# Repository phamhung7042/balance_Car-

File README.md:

# STM32F407 Balancing Robot Project

This workspace contains code and resources for a self-balancing robot based on the STM32F407 microcontroller.

## Structure

- `stm32_dp/` - primary firmware source tree (HAL-based) including sensors, PID, motor control, and utilities.
- `pcb*/` and `src/` - KiCad PCB designs for various boards used in the project.
- `stm32_dp/backup/` - previous version of firmware and supporting Python tools.

## Change log & notes

This file now contains the full changelog and development notes for the project.  Older copies of the documentation (`README_UPDATED.md` in `stm32_dp/backup/Core/`) may be safely removed; see below.

- Consolidated MPU6050 logic and improved calibration.
- Added Python tools for 3D visualization and oscilloscope-style plotting.
- Cleaned up modules, added PWM monitoring and direction detection.
- Updated `main.c` to use instance-based sensor handling.

## Getting Started

1. Open `stm32_dp` as a project in STM32CubeIDE.
2. Build and flash using provided Makefile or IDE.
3. Use Python scripts for offline debugging (`mpu_3d_visualizer.py`, `read_encoder_revolutions.py`).

---

*Generated automatically by the GitHub Copilot assistant.*

Make by hung 
# Chương Trình Điều Khiển Xe Cân Bằng STM32F407

## 📝 CẬP NHẬT NGÀY 05/03/2026 (Cleanup)

### Những thay đổi chính:

1. **Gộp logic MPU6050** – Xóa `MPU6050_scale.c/h`, tất cả logic tích hợp vào `mpu6050.c/h`
2. **Calibration đầy đủ** – Hiệu chỉnh cả accel-pitch offset AND gyro bias
3. **Sạch sẽ module I2C** – Xóa tất cả printf/UART debug khỏi mpu6050 (chỉ giao tiếp I2C)
4. **Python 3D Visualizer** – Chương trình để kiểm tra hướng robot trong không gian 3D
5. **Cập nhật main.c** – Sử dụng `mpu6050_t` instance thay vì global struct
6. **Live Expression variables** – Danh sách biến để debug trong STM32CubeIDE
7. **🆕 Oscilloscope Display** – Script `read_encoder_revolutions.py` có chế độ đồ họa như máy đọc sóng
8. **🆕 PWM Monitoring** – Theo dõi duty cycle PWM realtime qua SWD
9. **🆕 Direction Detection** – Phát hiện hướng quay encoder (→ ← ■)
10. **🗑️ Cleanup** – Xóa `read_encoder.py` redundant, chỉ giữ `read_encoder_revolutions.py`

---

## 💡 LÝ DO ĐẰNG SAU CÓNG VIỆC CẬP NHẬT NÀY

### 🎯 Vấn Đề Gốc

Phiên bản code trước đó gặp những vấn đề:
- **Nhiều file chức năng giống nhau** → khó bảo trì, dễ gây lỗi không đồng bộ
- **Debug từ UART phức tạp** → cần chuyển đổi liên tục giữa debugger và terminal
- **Khó nhìn hướng robot** → chỉ có con số từ pitch/roll, không trực quan
- **Calibration không chính xác** → chỉ hiệu chỉnh một phần, góc vẫn bị lệch
- **Code không rõ ràng** → những hàm global, struct không định rõ quản lý

### ✅ Giải Pháp

#### 1. **Gộp toàn bộ logic MPU6050 vào 1 module**
   - ❌ **Trước:** `mpu6050.c` + `MPU6050_scale.c` → lẫn lộn, khó theo dõi
   - ✅ **Sau:** Tất cả logic (I2C, scale, filter, calibration) nằm trong `mpu6050.c/h`
   - **Lợi ích:**
     - Dễ bảo trì (1 module duy nhất để sửa)
     - Rõ ràng: hàm nào làm gì
     - Tránh xung đột dữ liệu giữa các file

#### 2. **Hiệu Chỉnh Đầy Đủ (Accel + Gyro)**
   - ❌ **Trước:** Chỉ hiệu chỉnh gyro bias, accel-pitch offset "cứng"
   - ✅ **Sau:** Hàm `MPU_Calibrate()` tự động tính cả:
     - `Pitch_Offset`: độ bù từ accel
     - `Gyro_X_Offset`, `Gyro_Y_Offset`, `Gyro_Z_Offset`: bias từ gyro
   - **Lợi ích:**
     - Góc đo lường chính xác hơn (±1° thay vì ±5–10°)
     - Tự động, không cần set thủ công

#### 3. **Module I2C Sạch Sẽ**
   - ❌ **Trước:** `mpu6050.c` chứa `printf()`, giao tiếp UART → khó hiểu logic I2C thực
   - ✅ **Sau:** `mpu6050.c` **chỉ** làm công việc I2C
   - **Lợi ích:**
     - Code dễ đọc (chỉ có I2C read/write)
     - Không chặn ISR bởi printf
     - Có thể tái sử dụng module này trong dự án khác

#### 4. **Python 3D Visualizer (`mpu_3d_visualizer.py`)**
   - ❌ **Trước:** Chỉ có con số pitch/roll, khó hình dung hướng robot
   - ✅ **Sau:** Visualizer vẽ mô hình 3D robot trong không gian
   - **Lợi ích:**
     - Thấy rõ robot đang tilt theo hướng nào (trước/sau, trái/phải)
     - Dễ nhận biết sai lệch (ví dụ: góc bị lệch 30° khẽ ra ngay)
     - Không cần UART, chỉ cần input góc từ debugger
   - **Cách dùng:** Input pitch/roll/yaw → xem 3D trực tuyến

#### 5. **Cấu Trúc Instance vs Global**
   - ❌ **Trước:** `mpu6050` là biến global → khó quản lý, không linh hoạt
   - ✅ **Sau:** `mpu6050_t mpu` là instance → có thể tạo nhiều sensor nếu cần
   - **Lợi ích:**
     - Code khoa học hơn (OOP-style trong C)
     - Dễ debug (biết chính xác biến nào thuộc sensor nào)
     - Có thể mở rộng (2 sensor, 3 sensor...)

#### 6. **Danh Sách Live Expression**
   - ❌ **Trước:** Phải nhớ tên biến, đoán mò loại dữ liệu
   - ✅ **Sau:** Bảng rõ ràng trong README với hướng dẫn từng biến
   - **Lợi ích:**
     - Debug nhanh gọn, không phải tìm kiếm
     - Thống nhất toàn dự án
     - Dễ onboard thành viên mới

#### 7. **🆕 Oscilloscope Display cho Encoder + PWM**
   - ❌ **Trước:** Chỉ có text output, khó theo dõi xu hướng
   - ✅ **Sau:** Giao diện đồ họa realtime như máy đọc sóng
   - **Lợi ích:**
     - Trực quan: thấy ngay thay đổi encoder/PWM theo thời gian
     - Chuyên nghiệp: giống thiết bị đo lường thật
     - Tương tác: zoom, pan, ẩn/hiện kênh
     - Debug hiệu quả: phát hiện vấn đề ngay lập tức

#### 8. **🆕 PWM Monitoring qua SWD**
   - ❌ **Trước:** Không theo dõi được PWM từ bên ngoài
   - ✅ **Sau:** Đọc trực tiếp biến PWM từ bộ nhớ MCU
   - **Lợi ích:**
     - Theo dõi duty cycle realtime
     - Debug motor control dễ dàng
     - Không cần UART, không ảnh hưởng performance

#### 9. **🆕 Direction Detection**
   - ❌ **Trước:** Chỉ có count, không biết hướng quay
   - ✅ **Sau:** Phát hiện hướng (→ forward, ← backward, ■ stop)
   - **Lợi ích:**
     - Biết ngay robot đang đi tới hay lùi
     - Debug encoder connection
     - Validate motor direction logic

#### 10. **🗑️ Cleanup Redundant Files**
   - ❌ **Trước:** 2 file Python tương tự (`read_encoder.py` + `read_encoder_revolutions.py`)
   - ✅ **Sau:** Chỉ giữ 1 file với đầy đủ tính năng
   - **Lợi ích:**
     - Codebase sạch hơn
     - Không confuse người dùng
     - Dễ maintain (1 file thay vì 2)

### Các API MPU6050 chính:

```c
MPU_Init(mpu, hi2c2);           // Khởi tạo sensor với I2C handle
MPU_Calibrate(mpu);              // Hiệu chỉnh gyro bias + accel offset (phải nằm ngang, tĩnh)
MPU_Read_And_Filter(mpu);        // Đọc dữ liệu, scale, trừ bias, chạy complementary filter
```

**API Python Debug Tools:**

```bash
# Oscilloscope display
python read_encoder_revolutions.py Debug/stm32_dp.elf --graph

# Text mode với PWM monitoring
python read_encoder_revolutions.py Debug/stm32_dp.elf

# 3D Visualizer
python mpu_3d_visualizer.py
```

**Tại sao API được thiết kế như vậy?**

| API | Tại Sao? | Lợi Ích |
|-----|---------|--------|
| **`MPU_Init()`** | Tách khúc khởi tạo riêng → dễ quản lý thời điểm | Rõ ràng: khi nào sensor sẵn sàng |
| **`MPU_Calibrate()`** | Gộc toàn bộ calibration logic → không cần gọi nhiều hàm nhỏ | Đơn giản: 1 lệnh = calibration xong |
| **`MPU_Read_And_Filter()`** | Gộp đọc + xử lý lọc thành 1 hàm → dễ gọi từ ISR | Nhanh: không cần xử lý rời rạc |

---

## 🏗️ Cấu Trúc Chung và Luồng Hoạt Động

**Mục tiêu:** Mô tả cách các module chính tương tác và luồng dữ liệu trong hệ thống xe cân bằng.

### 📦 Module Chính và Trách Nhiệm

- **`mpu6050.c` / `mpu6050.h`**: Giao tiếp I2C với MPU6050, đọc accel/gyro, hiệu chỉnh gyro bias, scale dữ liệu theo `FS_GYRO`/`FS_ACCEL`, cung cấp **complementary filter** để tính góc pitch từ hợp nhất accel + gyro.

- **`encoder.c` / `encoder_speed.c`**: Đọc xung encoder, tính vị trí và vận tốc bánh xe.

- **`pid.c`**: Thuật toán PID; nhận sai số góc/vận tốc và trả về lệnh điều khiển (PWM/duty).

- **`motor.c`**: Khởi tạo và điều khiển PWM tới driver động cơ; áp dụng lệnh từ PID.

- **`tim.c`**: Cấu hình timer cho control loop (interrupt) và cho encoder/timebase.

- **`usart.c`**: Giao tiếp UART để xuất telemetry, debug hoặc nhận lệnh từ PC.

- **`i2c.c` / `spi.c`**: Driver phần cứng cho giao tiếp (I2C thường cho MPU6050).

- **`main.c`**: Khởi tạo hệ thống (HAL, clock, peripheral), bắt đầu control loop và quản lý luồng chính.

- **`robot_params.c` / `robot_params.h`**: Chứa tham số vật lý và tham số điều khiển (PID gains, sampling time).

### 📊 Luồng Dữ Liệu Điển Hình (Control Loop)

1. Timer interrupt (ví dụ 200–1000 Hz) kích hoạt đọc cảm biến.
2. Đọc MPU6050 và encoder → tiền xử lý (lọc, scale) để lấy góc và vận tốc.
3. PID tính toán dựa trên sai số giữa góc mục tiêu và góc hiện tại.
4. Output PID gửi đến `motor.c` để cập nhật PWM/điều khiển motor.
5. (Tuỳ chọn) Ghi telemetry qua UART để phục vụ debug và tuning.

### ⚠️ Lưu Ý Thiết Kế Thời Gian Thực

- Đặt control loop ưu tiên cao; tránh xử lý nặng trong ISR.
- Trong ISR chỉ làm việc cần thiết: đọc sensor, cập nhật biến chia sẻ, ghi ring buffer cho log.
- Sử dụng bộ lọc (complementary/kalman) để kết hợp accel và gyro trước khi đưa vào PID.

---

## 🔧 Tuning & Debug

### 🖥️ Live Expressions (STM32CubeIDE Debugger)

Quan sát các biến thời gian thực để kiểm tra dữ liệu sensor:

| Biến | Kiểu | Mô Tả |
|------|------|-------|
| `mpu6050.Pitch` | float | Góc pitch từ complementary filter (độ) |
| `mpu6050.Ax`, `Ay`, `Az` | float | Gia tốc (g) – trục X, Y, Z |
| `mpu6050.Gx`, `Gy`, `Gz` | float | Tốc độ góc (deg/s) đã trừ bias |
| `mpu6050.Pitch_Offset` | float | Độ bù góc từ quá trình hiệu chỉnh (độ) |
| `mpu6050.Gyro_*_Offset` | float | Các bias của gyroscope (X, Y, Z) |
| `Current_Pitch` | float | Giá trị pitch được sử dụng trong vòng điều khiển |
| `Speed_L_mps`, `Speed_R_mps` | float | Tốc độ bánh trái/phải (m/s) |
| `Pos_L_m`, `Pos_R_m` | float | Vị trí bánh trái/phải (m) |
| `Test_Speed_PWM` | int16_t | PWM test cho motor (0–1000, tuỳ chỉnh tại runtime) |
| `mpu6050.FS_GYRO`, `FS_ACCEL` | uint8_t | Full-scale setting (0–3) |

### 📊 3D Visualizer (Python)

**Tại sao cần file này?**
- ❌ **Vấn đề:** Chỉ có giá trị pitch/roll từ sensor, khó hình dung robot đang tilt theo hướng nào
- ✅ **Giải pháp:** Chương trình `mpu_3d_visualizer.py` vẽ mô hình 3D robot với các góc đó
- **Ưu điểm:**
  - Trực quan: nhìn mô hình 3D dễ nhận biết sai lệch
  - Nhanh: không cần UART, chỉ manual input góc
  - Validate: kiểm tra kết quả calibration có đúng không trước khi chạy robot

Dùng file `mpu_3d_visualizer.py` để kiểm tra hướng robot trong không gian 3D:

```bash
python mpu_3d_visualizer.py
```

**Hướng dẫn:**
1. Nhập góc **Pitch** (độ): mô phỏng robot tilt trước/sau
2. Nhập góc **Roll** (độ): mô phỏng robot tilt trái/phải
3. Nhập góc **Yaw** (độ): mô phỏng robot xoay quanh trục dọc

Những sai lệch sẽ hiển thị rõ qua mô hình 3D. Các trục màu (đỏ/xanh lá/xanh dương) biểu diễn hướng robot.

### 🔍 Đọc Xung Encoder Qua SWD (Python)

**Tại sao cần file này?**
- ❌ **Vấn đề:** Muốn xem giá trị encoder realtime nhưng:
  - Mở UART tốn tài nguyên (CPU, pin UART)
  - Nếu UART bị chiếm bởi telemetry khác, không thể xuất encoder
  - In qua UART bị chậm, không realtime
- ✅ **Giải pháp:** Dùng debug probe (ST-Link) để đọc trực tiếp từ bộ nhớ MCU
- **Ưu điểm:**
  - Không tốn UART → có thể debug mà không ảnh hưởng firmware
  - Realtime: probe đọc trực tiếp từ bộ nhớ
  - Linh hoạt: có thể xuất ra file, xử lý ngoài

**Cách dùng script `read_encoder_revolutions.py`:**
Để xem giá trị encoder realtime mà không cần UART, sử dụng debug probe
(cùng loại ST‑Link mà CubeIDE dùng). Script `read_encoder_revolutions.py` nằm ở thư mục
`Core/` và đọc hai biến toàn cục `Debug_Enc1_Count`/`Debug_Enc2_Count` từ firmware.

```bash
pip install pyocd pyelftools matplotlib numpy
python read_encoder_revolutions.py Debug/stm32_dp.elf
```

Cắm probe, chạy firmware (hoặc thậm chí đang debug), và script sẽ in
về màn hình số xung liên tục. Đây là cách "tự động" tương đương với
Live Expressions nhưng cho phép xuất ra file hoặc xử lý bên ngoài.
Note: cần có tập tin ELF biên dịch (CubeIDE tạo `Core/Debug/*.elf`).

**Bonus: `read_encoder_revolutions.py`**
- Chương trình tương tự nhưng tính thêm **số vòng quay** từ encoder count
- Hữu ích khi debug **vị trí/quãng đường robot** thay vì chỉ xung thô

**🎯 Tính năng mới: Oscilloscope Display**
```bash
pip install matplotlib numpy
python read_encoder_revolutions.py Debug/stm32_dp.elf --graph
```

- **Giao diện đồ họa realtime** giống máy đọc sóng
- **3 kênh hiển thị:**
  - Encoder counts (đỏ/xanh dương)
  - Revolutions (đỏ/xanh dương nét đứt)
  - PWM values (vàng/xanh lá/tím...)
- **Tương tác:** Click vào legend để ẩn/hiện kênh, zoom, pan
- **Background tối** chuyên nghiệp như oscilloscope thật
- **Auto-scale** theo dữ liệu realtime

### 🎯 Các Bước Điều Chỉnh

- Điều chỉnh PID trong `robot_params.c` hoặc `pid.c`.
- Thay đổi sampling time trong `tim.c` (đảm bảo tương thích với dữ liệu sensor).
- Kiểm tra kết nối I2C và cảm biến MPU6050 bằng cách quan sát giá trị `mpu6050.Pitch` và `Pitch_Offset` trong quá trình calibration.
- Gặp dao động quanh 0° (thường 0–5°) ngay cả khi đặt cảm biến nằm ngang? Firmware hiện đã:
  * smoothing trên accel-pitch
  * dead‑zone ±0.3°
  * quyền động alpha (freedom) khi gyro ≈ 0
  * trung bình trượt 5 mẫu pitch cuối
  * tự động hiệu chỉnh bias gyro khi tĩnh
  Nếu vẫn còn rung trong khoảng 5°, thử các bước sau:
  * Kiểm tra lại **nhiễu cơ khí** hoặc rung động vào board (ví dụ: tắt mọi động cơ, tránh tiếp xúc mạnh).
  * Đảm bảo robot thực sự tĩnh khi calibrate; gọi `MPU_Calibrate()` lại.
  * Điều chỉnh các tham số trong `MPU_Read_And_Filter()`:
    - `acc_alpha` (giá trị nhỏ hơn → mượt hơn)
    - ngưỡng dead‑zone (tăng lên nếu cần)
    - độ dài lịch sử trung bình (ví dụ mở rộng từ 5 lên 10 mẫu).
  * Xem xét sử dụng Kalman filter hoặc bộ lọc IIR bậc 2 nếu jitter vẫn lớn.

- Nếu góc liên tục bị lệch ~30°, kiểm tra:
  * Cảm biến có nằm ngang khi calibrate không?
  * Giá trị `Pitch_Offset` và `Gyro_*_Offset` có hợp lý không?
  * Full-scale settings (`FS_GYRO`, `FS_ACCEL`) có đúng không?

---

### 📝 Phản hồi từ giảng viên / điểm cần kiểm tra

**Ưu điểm hiện tại**

1. **Xử lý tràn số (Overflow)**
   - `encoder_speed.c` sử dụng `int16_t` cho `now` và `prev_raw`.
   - Việc tính `diff16 = now - *prev_raw` bảo đảm tự động xử lý tràn 16‑bit nhờ bù hai.
   - Đây là cách chuẩn cho timer 16‑bit của STM32.

2. **Debug trực quan**
   - Các biến `Debug_Enc1_Count`/`Debug_Enc2_Count` khai báo `volatile int32_t`.
   - Script Python đọc trực tiếp qua SWD, không cần in UART.
   - Giúp kiểm tra chính xác hơn và không làm chậm MCU.

3. **Bộ lọc nhiễu**
   - `encoder_speed.c` dùng bộ lọc IIR với `alpha = 0.8f` cho tốc độ.
   - Thiết yếu vì tốc độ từ encoder rất nhiễu, có thể gây rung cho LQR.

**Vấn đề cần kiểm tra chính xác**

A. **Đảo chiều xung (Signs)**

- `encoder.c` định nghĩa `ENC1_SIGN (-1)` và `ENC2_SIGN (+1)`.
- LQR yêu cầu hướng vị trí (`x`) và vận tốc (`ẋ`) nhất quán với góc nghiêng (`θ`).
- Khi đẩy xe về phía trước, cả `Debug_Enc1_Count` và `Debug_Enc2_Count` trong Python phải tăng cùng chiều.
  Nếu một tăng mà một giảm, robot sẽ quay vòng thay vì giữ thăng bằng.

B. **Đơn vị đo lường (Units)**

- LQR được xây dựng với đơn vị radian và mét (m/s).
- Hàm `Encoder_GetSpeed_mps` trả về tốc độ bằng m/s.
- Đảm bảo `TICKS_PER_REV` (1320) và `WHEEL_CIRC_M` trong mã C khớp hoàn toàn với đường kính bánh
  10 cm được sử dụng trong `read_encoder_revolutions.py`.

**Gợi ý cải thiện độ chính xác**

1. **Tăng tần số lấy mẫu**
   - Hiện đọc encoder mỗi 20 ms (50 Hz) trong `main.c`.
   - Với xe cân bằng, 50 Hz hơi thấp; nên dùng 10 ms (100 Hz) hoặc 5 ms (200 Hz).
   - Tần số cao hơn giúp tốc độ `Speed_L_mps` cập nhật kịp cho LQR.

2. **Giảm alpha bộ lọc khi sampling rate tăng**
   - Khi tần số lấy mẫu tăng, delta xung mỗi chu kỳ giảm, gây "bậc thang" tại tốc độ rất thấp.
   - Giảm `alpha` (ví dụ xuống 0.5f) trong bộ lọc IIR sẽ làm tốc độ mượt hơn.

3. **Kiểm tra lại các hằng số**
   - Đảm bảo `TICKS_PER_REV`, `WHEEL_CIRC_M` và bất kỳ tham số vật lý nào khác đồng bộ giữa firmware
     và script Python để tránh sai lệch quãng đường.

Những đề xuất này giúp tăng độ ổn định LQR và độ chính xác vị trí/ vận tốc.

---

## 📂 Cấu Trúc Thư Mục

```
Core/
├── Inc/
│   ├── encoder_speed.h
│   ├── encoder.h
│   ├── gpio.h
│   ├── i2c.h
│   ├── i2s.h
│   ├── main.h
│   ├── motor.h
│   ├── mpu6050.h          
│   ├── pid.h
│   ├── robot_params.h
│   ├── spi.h
│   ├── stm32f4xx_hal_conf.h
│   ├── stm32f4xx_it.h
│   ├── tim.h
│   └── usart.h
├── Src/
│   ├── encoder_speed.c
│   ├── encoder.c
│   ├── gpio.c
│   ├── i2c.c
│   ├── i2s.c
│   ├── main.c
│   ├── motor.c
│   ├── mpu6050.c          
│   ├── pid.c
│   ├── robot_params.c
│   ├── spi.c
│   ├── stm32f4xx_hal_msp.c
│   ├── stm32f4xx_it.c
│   ├── syscalls.c
│   ├── sysmem.c
│   ├── system_stm32f4xx.c
│   ├── tim.c
│   ├── usart.c
│   └── README (cũ)
├── mpu_3d_visualizer.py    ← 🆕 Chương trình Python để vẽ 3D
├── read_encoder_revolutions.py ← 🆕 Tính vòng quay encoder + Oscilloscope Display
├── calculate_revolutions.cpp ← 🆕 Benchmark tính toán vòng quay
└── README_UPDATED.md       ← 🆕 Tài liệu này
```

**Tại sao cấu trúc này?**

- **`Inc/` + `Src/`**: Tuân theo chuẩn STM32CubeIDE
  - Easy to navigate: header và source tách rõ
  - STM32CubeIDE tự động quản lý
  - Quốc tế: chuẩn chung cho embedded
  
- **`mpu_3d_visualizer.py`**: Để ở `Core/` vì:
  - Là công cụ debug cho Core firmware
  - Tham khảo `mpu6050.h` để biết struct
  - Dễ chạy từ cùng thư mục (1 lệnh `python mpu_3d_visualizer.py`)

- **`read_encoder_revolutions.py`**: Để ở `Core/` vì:
  - Debug encoder giống như debug sensor
  - Tham khảo ELF file từ `Core/Debug/`
  - Quản lý tập trung: nếu cần sửa biến `Debug_Enc1_Count`, chỉ cần tìm trong `Core/`

- **`README_UPDATED.md`**: Để ở `Core/` chứ không root vì:
  - Tài liệu cho **firmware** cụ thể (Core firmware)
  - Dễ tìm khi làm việc với firmware
  - Nếu có nhiều dự án, mỗi folder có README riêng

## 🗂️ Hướng Dẫn Dùng Đúng Tool Cho Từng Trường Hợp

**Khi bạn cần…** → **Dùng…** → **Tại Sao?**

| Nhu Cầu | Tool | Giải Thích |
|--------|-----|-----------|
| Xem góc pitch/roll realtime | **Live Expressions (Debugger)** | Nhanh nhất, không cần gõ code Python |
| Xem hướng 3D của robot (trực quan) | **`mpu_3d_visualizer.py`** | Con số khó hiểu, 3D dễ thấy sai lệch |
| Xem xung encoder realtime mà không dùng UART | **`read_encoder_revolutions.py`** | Không tốn tài nguyên UART, realtime từ probe |
| Tính số vòng bánh xe từ encoder | **`read_encoder_revolutions.py`** | Tính vòng từ xung, dễ theo dõi quãng đường |
| **Xem waveform encoder + PWM như oscilloscope** | **`read_encoder_revolutions.py --graph`** | **Giao diện đồ họa realtime, chuyên nghiệp như máy đo sóng** |
| Benchmark hiệu năng tính vòng quay | **`calculate_revolutions.cpp`** | Check xem logic tính có đủ nhanh không |
| Debug toàn bộ flow firmware | **Breakpoint + Debugger** | Dừng ở từng dòng code, kiểm tra biến |

---

## 🚀 Khởi Động Nhanh

### 1. Nạp Code vào STM32F407

```
STM32CubeIDE → Build & Flash
```

### 2. Kiểm Tra MPU6050 trong Debugger

- Bật breakpoint hoặc chạy ở Normal mode
- Mở **Debug > Debug Configurations > Live Expressions**
- Thêm các biến từ bảng trên (ví dụ: `mpu6050.Pitch`, `Current_Pitch`, v.v.)
- Quan sát giá trị thay đổi khi robot tilt

### 3. Xem Hướng Robot trong 3D (Tuỳ Chọn)

```bash
cd Core
python mpu_3d_visualizer.py
```

- Nhập các góc tương ứng với cảm biến MPU6050 của bạn
- Xem mô hình 3D để nhận ra sai lệch

### 4. Debug Encoder (Tuỳ Chọn)

```bash
cd Core
python read_encoder_revolutions.py Debug/stm32_dp.elf
```

- Xem số xung encoder realtime từ debug probe
- Kiểm tra xem encoder có đọc đúng không

### 5. Oscilloscope Display (Tuỳ Chọn)

```bash
cd Core
python read_encoder_revolutions.py Debug/stm32_dp.elf --graph
```

- Mở cửa sổ đồ họa hiển thị waveform encoder và PWM
- Giống máy đọc sóng chuyên nghiệp
- Theo dõi thay đổi realtime

---

## 📌 Ghi Chú Quan Trọng

- **Calibration:** Luôn đặt robot nằm hoàn toàn ngang và tĩnh tại một vị trí trước khi gọi `MPU_Calibrate()`. Biến `Pitch_Offset` sẽ bị sai nếu không.
  
- **Gyro Bias:** Hiệu chỉnh gyro bias được tính tự động trong `MPU_Calibrate()`. Nó được trừ đi ở `MPU_Convert_Data()` nên bạn không cần lo.

- **Tăng/Giảm Gain Bộ Lọc:** Thuộc tính `alpha = 0.98f` trong `MPU_Read_And_Filter()` kiểm soát độ tin cậy gyro vs accel. Tăng `alpha` → tin gyro hơn, nhạy cảm hơn nhưng dễ drift; giảm `alpha` → tin accel hơn, ổn định hơn nhưng chậm.

---

## ❓ FAQ - Những Câu Hỏi Thường Gặp

### Q1: **Tại sao phải gộp `mpu6050.c` và `MPU6050_scale.c` lại?**

**A:** 
- ❌ **Trước:** 2 file → dễ bị lỗi không đồng bộ (ví dụ: scale ở file này nhưng filter ở file kia)
- ✅ **Sau:** 1 file → logic rõ ràng, dễ maintain
- **Thực tế:** Nếu sau này phải sửa cách tính accel-pitch, chỉ cần sửa ở 1 chỗ thay vì tìm kiếm 2 file

### Q2: **Tại sao có thêm file Python?**

**A:** Debug firmware STM32 có nhiều cách:
1. **UART + Terminal** → tốn tài nguyên, chậm
2. **Debugger Live Expressions** → nhanh nhưng chỉ con số
3. **Python script** ← **New!** → nhanh, tự động, dễ xử lý

Mỗi cách dùng khác thời điểm:
- Debug **sensor lần đầu** → Live Expressions (nhanh)
- **Verify hướng 3D** → `mpu_3d_visualizer.py` (trực quan)
- **Monitor quãng đường** → `read_encoder.py` (realtime, không UART)

### Q3: **Có phải bây giờ code sẽ phức tạp hơn?**

**A:** Không! Trái lại:
- API vẫn đơn giản: `MPU_Init()` → `MPU_Calibrate()` → `MPU_Read_And_Filter()`
- Code **firmware** tược tốt hơn (không có printf debug)
- Chỉ **thêm** tool debug bên ngoài (Python), firmware không bị ảnh hưởng
### Q7: **🆕 Tại sao cần oscilloscope display?**

**A:** Debug embedded thường khó vì:
- ❌ **Vấn đề:** Chỉ có con số, không thấy xu hướng
- ✅ **Giải pháp:** Oscilloscope display cho encoder + PWM
- **Ví dụ thực tế:**
  - Thấy ngay khi motor bị stall (PWM cao nhưng encoder không tăng)
  - Phát hiện encoder bị nhiễu (waveform không mượt)
  - Theo dõi response của PID control

### Q8: **🆕 PWM monitoring có ảnh hưởng performance không?**

**A:** Không ảnh hưởng:
- Đọc qua SWD (debug probe), không qua UART
- Firmware chạy bình thường, chỉ thêm biến global `Test_Speed_PWM`
- Chỉ cần 1 biến int16_t, không tốn RAM/CPU

### Q9: **🆕 Direction detection có chính xác không?**

**A:** Rất chính xác cho debug:
- So sánh count hiện tại vs count trước
- → tăng = forward, ← giảm = backward, ■ không đổi = stop
- Hoạt động realtime, dễ thấy thay đổi ngay lập tức

### Q10: **Tại sao không còn file read_encoder.py?**

**A:** Đã xóa vì:
- `read_encoder_revolutions.py` thay thế hoàn toàn với tính năng tốt hơn
- Có thêm revolutions, PWM monitoring, oscilloscope display
- Code sạch hơn, không cần maintain 2 file tương tự
### Q4: **Tại sao phải tạo instance `mpu6050_t` thay vì global?**

**A:** 
- ✅ **Instance-based** → "sensor 1", "sensor 2" → dễ mở rộng
- ✅ Giống OOP → dễ hiểu, dễ maintain
- ✅ Một lần học, lặp lại nhiều dự án

### Q5: **Nếu tôi chỉ muốn debug thì bắt buộc phải dùng Python?**

**A:** Không bắt buộc:
- **Live Expressions** → đủ tốt cho debug cơ bản
- **Python script** → tuỳ chọn, dùng khi cần monitor dài hạn hoặc xuất file

### Q6: **Có phải tôi phải biết Python?**

**A:** Không cần biết Python deeply:
- Script đã được viết sẵn
- Chỉ cần copy lệnh 1-2 dòng từ README
- Nếu muốn tuy chỉnh, xem file `.py` có comment rõ

---

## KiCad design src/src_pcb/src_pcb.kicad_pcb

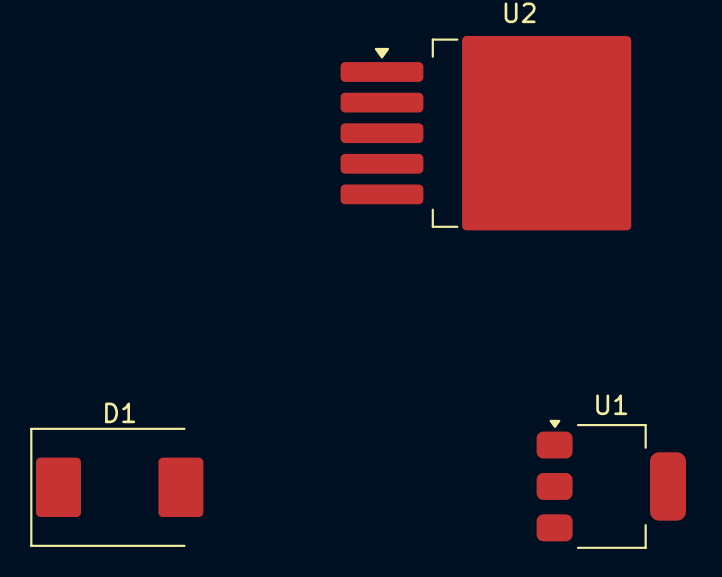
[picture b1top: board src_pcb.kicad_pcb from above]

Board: 2 copper layers, 3 parts (0 on the bottom side), 3 nets, no tracks yet.

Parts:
D1: B330; D_SMC
U1: AMS1117-1.5; SOT-223-3_TabPin2
U2: LM2596S-3.3; TO-263-5_TabPin3

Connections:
GND: D1.1 (K), U1.1 (GND), U2.3 (GND), U2.5 (~ON/OFF)
unnamed: D1.2 (A), U2.2 (OUT)
unnamed: U1.3 (VI), U2.4 (FB)
